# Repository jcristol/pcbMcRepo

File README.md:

# pcbMcRepo
A hearty and fully functional meal from the fryer of Texas Guadaloop Industries Ltd. Limited time supply

- See the circuit schematic look at .sch files
- See the PCB layout look at .pcb files
- Open these files I suggest you use KiCAD
- The circuit below is the myrio circuit

### Picture of the PCB

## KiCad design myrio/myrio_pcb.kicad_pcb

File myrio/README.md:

# pcbMcRepo
A hearty and fully functional meal from the fryer of Texas Guadaloop Industries Ltd. Limited time supply

### [Google Doc](https://docs.google.com/document/d/14EoQXWibSE1bEbYZ6znybRfnlsqGPjPEWS3_kOOsmus/edit)

## Work Division
__3 branch__ 

__Cody__

__Josh__

__Master merge on agreement__

### Design Comments feel free to edit

## BLOCKERS
1. Screw Terminals footprints need to be exact so the labels will fit
2. Ethernet Pin outs
3. Do we need pull up resistors on the bus?
4. The i2c stress test. Are the buses too full?
5. Specs on the housing for the myrio pinout on the PCB
6. Measure the diameter of the vin+ and vin- pins
7. Pin out on the power converters?

## EXTRA Features
1. Cody had special connectors for the robot car that we can use for the power and end connection
2. The screw terminals for extra shit

## Ben Questions
__Ethernet Pin Outs__

__i2c stress test how did that go?__ 

__Are the i2c buses full and will this change the PCB design?__

__Do we need Pull up resistors on the bus?__

__Measure the diameter of power board vin+ and vin- pins__

__Pin out on the par converters i.e. vin, gnd, vout+, vout-__

__Details on what extra screw terminals we need and how you want them arranged?__

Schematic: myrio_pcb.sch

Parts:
220ohm1, 220ohm2, 220ohm3, 220ohm4: R; R_Axial_DIN0204_L3.6mm_D1.6mm_P5.08mm_Horizontal
C1, C2, C3, C4, C5, C6, C7, C9: C; CP_Radial_D5.0mm_P2.50mm
D1, D2, D3, D4, D5, D6, D7, D8, D9, D10, D11, D12, D13, D14, D15, D16, D17, D18, D19, D20, D22: D; D_DO-35_SOD27_P5.08mm_Vertical_AnodeUp
D23: LED; LED_D5.0mm
H1: BMP180; bmp180
J1, J2, J3, J4: CONN_02X03; Pin_Header_Straight_2x03_Pitch2.54mm
P1, P2: CONN_02X17; Socket_Strip_Straight_2x17_Pitch2.54mm
Q1, Q2, Q3, Q4, Q5, Q6, Q7, Q8, Q9, Q10, Q11, Q12, Q13, Q14, Q15, Q16, Q17, Q18, Q19, Q20: PN2222A; TO-92_Inline_Narrow_Oval
R1, R2, R3, R4, R5, R6, R7, R8, R9, R10, R11, R12, R13, R14, R15, R16, R17, R18, R19, R20, R22, R23, R24, R25, R26, R27, R28, R29: R; R_Axial_DIN0204_L3.6mm_D1.6mm_P5.08mm_Horizontal
R21: 500; R_Axial_DIN0204_L3.6mm_D1.6mm_P5.08mm_Horizontal
R30, R31: 12K; R_Axial_DIN0204_L3.6mm_D1.6mm_P5.08mm_Horizontal
R32, R33: 2K; R_Axial_DIN0204_L3.6mm_D1.6mm_P5.08mm_Horizontal
RE1, RE2, RE3, RE4, RE5, RE6, RE7, RE8, RE9, RE10, RE11, RE12, RE13, RE14, RE15, RE16, RE17, RE18, RE19, RE20: relay
S2, S4, S5, S6: 2pinscrew; screwinconnector++
T1, T2, T3, T4: Phoenix_Contact_1935187
U1, U2, U8: stacked-DB9; DB9-doublestacked_PR
U3, U4, U5, U7, U14, U15: stacked-rj45-LED; stacked-rj45_Final++
U6: BNO055
U10, U11, U13: INA219

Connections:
2way_close_1: RE6.1 (NC), U14.2
2way_close_2: RE7.1 (NC), U14.5
2way_close_3: RE8.1 (NC), U14.10
2way_ctrl_1: P1.11, R1.2
2way_ctrl_1_coil-: D1.2 (A), Q1.3 (C), RE6.9 (coil-)
2way_ctrl_2: P1.13, R2.2
2way_ctrl_2_coil-: D2.2 (A), Q2.3 (C), RE7.9 (coil-)
2way_ctrl_3: P1.15, R3.2
2way_ctrl_3_coil-: D3.2 (A), Q3.3 (C), RE8.9 (coil-)
2way_open_1: RE6.10 (NO), U14.1
2way_open_2: RE7.10 (NO), U14.4
2way_open_3: RE8.10 (NO), U14.9
3way_close_1: RE14.1 (NC), U14.13
3way_close_2: RE16.1 (NC), U15.2
3way_ctrl_1a: P1.17, R9.2
3way_ctrl_1a_coil-: D9.2 (A), Q9.3 (C), RE14.9 (coil-)
3way_ctrl_1b: P1.19, R15.2
3way_ctrl_1b_coil-: D15.2 (A), Q15.3 (C), RE13.9 (coil-)
3way_ctrl_2a: P1.21, R10.2
3way_ctrl_2a_coil-: D10.2 (A), Q10.3 (C), RE16.9 (coil-)
3way_ctrl_2b: P1.23, R16.2
3way_ctrl_2b_coil-: D16.2 (A), Q16.3 (C), RE15.9 (coil-)
3way_port2_1: RE13.1 (NC), U14.12
3way_port2_2: RE15.1 (NC), U15.1
3way_port3_1: RE13.10 (NO), U14.15
3way_port3_2: RE15.10 (NO), U15.3
5V: D1.1 (K), D2.1 (K), D3.1 (K), D4.1 (K), D5.1 (K), D6.1 (K), D7.1 (K), D8.1 (K), D9.1 (K), D10.1 (K), D11.1 (K), D12.1 (K), D13.1 (K), D14.1 (K), D15.1 (K), D16.1 (K), D17.1 (K), D18.1 (K), D19.1 (K), D20.1 (K), R22.1, R23.1, R24.1, R25.1, R26.1, R27.1, R28.1, R29.1, RE1.2 (coil+), RE1.10 (NO), RE2.2 (coil+), RE2.10 (NO), RE3.2 (coil+), RE3.10 (NO), RE4.2 (coil+), RE4.10 (NO), RE5.2 (coil+), RE6.2 (coil+), RE7.2 (coil+), RE8.2 (coil+), RE9.2 (coil+), RE9.10 (NO), RE10.2 (coil+), RE10.10 (NO), RE11.2 (coil+), RE11.10 (NO), RE12.2 (coil+), RE12.10 (NO), RE13.2 (coil+), RE14.2 (coil+), RE15.2 (coil+), RE16.2 (coil+), RE17.2 (coil+), RE17.10 (NO), RE18.2 (coil+), RE19.2 (coil+), RE20.2 (coil+), T3.4
12V: C1.1, C2.1, T1.1, T3.1, T4.3, U10.8 (VIN+), U11.7 (VIN-)
24V: C4.1, C9.1, RE5.10 (NO), T1.4, U7.1, U7.4, U8.9, U8.11, U13.8 (VIN+), U15.7, U15.8, U15.11, U15.14
24V_activation: RE5.5 (load1), RE5.6 (load2), RE6.5 (load1), RE6.6 (load2), RE7.5 (load1), RE7.6 (load2), RE8.5 (load1), RE8.6 (load2), RE14.5 (load1), RE14.6 (load2), RE16.5 (load1), RE16.6 (load2)
A0: P2.3, S2.1
A1: P2.5, S2.2
DGND: 220ohm1.2, 220ohm2.2, 220ohm3.2, 220ohm4.2, C1.2, C2.2, C3.2, C4.2, C5.2, C6.2, C7.2, C9.2, H1.2 (gnd), P1.6, P1.8, P1.12, P1.16, P1.20, P1.24, P1.28, P1.30, P2.6, P2.8, P2.12, P2.16, P2.20, P2.24, P2.28, P2.30, Q1.1 (E), Q2.1 (E), Q3.1 (E), Q4.1 (E), Q5.1 (E), Q6.1 (E), Q7.1 (E), Q8.1 (E), Q9.1 (E), Q10.1 (E), Q11.1 (E), Q12.1 (E), Q13.1 (E), Q14.1 (E), Q15.1 (E), Q16.1 (E), Q17.1 (E), Q18.1 (E), Q19.1 (E), Q20.1 (E), R21.2, R32.2, R33.2, RE1.1 (NC), RE2.1 (NC), RE3.1 (NC), RE4.1 (NC), RE9.1 (NC), RE10.1 (NC), RE11.1 (NC), RE12.1 (NC), RE17.1 (NC), RE19.1 (NC), RE20.1 (NC), S6.2, T1.2, T1.3, T2.2, T2.4, T3.2, T3.3, T4.4, U1.5, U1.6, U1.7, U1.8, U1.9, U1.14, U1.15, U1.16, U1.17, U1.18, U2.5, U2.6, U2.7, U2.8, U2.9, U2.14, U2.15, U2.16, U2.17, U2.18, U3.2, U3.5, U3.10, U3.13, U4.2, U4.5, U4.10, U4.13, U5.2, U5.5, U5.10, U5.13, U6.3 (gnd), U7.2, U7.5, U7.10, U7.13, U8.5, U8.12, U10.2 (Gnd), U11.2 (Gnd), U13.2 (Gnd), U14.3, U14.7, U14.11, U14.16, U15.6
unnamed: D23.1 (K), R21.1
unnamed: Q1.2 (B), R1.1
unnamed: Q2.2 (B), R2.1
unnamed: Q3.2 (B), R3.1
unnamed: Q4.2 (B), R4.1
unnamed: Q5.2 (B), R5.1
unnamed: Q6.2 (B), R6.1
unnamed: Q7.2 (B), R7.1
unnamed: Q8.2 (B), R8.1
unnamed: Q9.2 (B), R9.1
unnamed: Q10.2 (B), R10.1
unnamed: Q11.2 (B), R11.1
unnamed: Q12.2 (B), R12.1
unnamed: Q13.2 (B), R13.1
unnamed: Q14.2 (B), R14.1
unnamed: Q15.2 (B), R15.1
unnamed: Q16.2 (B), R16.1
unnamed: Q17.2 (B), R17.1
unnamed: Q18.2 (B), R18.1
unnamed: Q19.2 (B), R19.1
unnamed: Q20.2 (B), R20.1
unnamed: RE13.5 (load1), RE14.10 (NO)
unnamed: RE15.5 (load1), RE16.10 (NO)
Tof_Ctrl_1: P2.11, R5.2
Tof_Ctrl_1_coil-: D5.2 (A), Q5.3 (C), RE1.9 (coil-)
Tof_Ctrl_2: P2.13, R11.2
Tof_Ctrl_2_coil-: D11.2 (A), Q11.3 (C), RE9.9 (coil-)
Tof_Ctrl_3: P2.15, R6.2
Tof_Ctrl_3_coil-: D6.2 (A), Q6.3 (C), RE2.9 (coil-)
Tof_Ctrl_4: P2.17, R12.2
Tof_Ctrl_4_coil-: D12.2 (A), Q12.3 (C), RE10.9 (coil-)
Tof_Ctrl_5: P2.19, R7.2
Tof_Ctrl_5_coil-: D7.2 (A), Q7.3 (C), RE3.9 (coil-)
Tof_Ctrl_6: P2.21, R13.2
Tof_Ctrl_6_coil-: D13.2 (A), Q13.3 (C), RE11.9 (coil-)
Tof_Ctrl_7: P2.23, R8.2
Tof_Ctrl_7_coil-: D8.2 (A), Q8.3 (C), RE4.9 (coil-)
Tof_Ctrl_8: P2.25, R14.2
Tof_Ctrl_8_coil-: D14.2 (A), Q14.3 (C), RE12.9 (coil-)
battery: C3.1, T2.3, T4.1
battery+fuse: C7.1, D23.2 (A), T4.2, U11.8 (VIN+)
brake_pwr: RE19.10 (NO), RE20.10 (NO), U13.7 (VIN-)
critical_scl: J1.6, J3.6, P2.32, R23.2, U3.3, U3.7, U3.11, U3.15
critical_sda: J2.6, J4.6, P2.34, R22.2, U3.6, U3.8, U3.14, U3.16
friction_coil-: D19.2 (A), Q19.3 (C), RE19.9 (coil-)
friction_ctrl: P1.27, R19.2
friction_pwr: RE18.5 (load1), RE18.6 (load2), RE19.5 (load1), RE19.6 (load2), U1.1, U1.2, U1.3, U1.4, U2.1, U2.2, U2.3, U2.4
i2c_scl_2: J1.2, J3.2, P2.22, R27.2, S4.1
i2c_scl_3: P1.22, R29.2, S5.1
i2c_sda_2: J2.2, J4.2, P2.26, R26.2, S4.2
i2c_sda_3: P1.26, R28.2, S5.2
laser1: P2.29, U7.11
laser2: P2.31, U7.15
laser_digital1: P2.18, R30.2, R33.1
laser_digital2: P1.25, R31.2, R32.1
magnetic_coil-: D20.2 (A), Q20.3 (C), RE20.9 (coil-)
magnetic_ctrl: P1.29, R20.2
magnetic_pwr: D22.2 (A), RE20.5 (load1), RE20.6 (load2), U1.10, U1.11, U1.12, U1.13, U2.10, U2.11, U2.12, U2.13
main_laser1: R30.1, U7.3
main_laser2: R31.1, U7.7
myRIO_12V: C5.1, T2.1, U10.7 (VIN-)
non_critical_scl: H1.3 (scl), J1.1, J3.1, P1.32, R25.2, U6.5 (scl), U10.3 (Scl), U11.3 (Scl), U13.3 (Scl)
non_critical_sda: H1.4 (sda), J2.1, J4.1, P1.34, R24.2, U6.4 (sda), U10.4 (Sda), U11.4 (Sda), U13.4 (Sda)
pressure1-: 220ohm1.1, P1.3, U15.4
pressure2-: 220ohm2.1, P1.5, U15.5
pressure3-: 220ohm3.1, P1.7, U15.9
pressure4-: 220ohm4.1, P1.9, U15.10
pressure_activation: P1.31, R4.2
pressure_activation_coil-: D4.2 (A), Q4.3 (C), RE5.9 (coil-)
sense_pwr: C6.1, H1.1 (5V), RE17.5 (load1), RE17.6 (load2), U5.1, U5.4, U5.9, U5.12, U6.1 (Vin), U7.9, U7.12, U10.1 (Vin), U11.1 (Vin), U13.1 (Vin)
sense_pwr_coil-: D18.2 (A), Q18.3 (C), RE17.9 (coil-)
sense_pwr_ctrl: P2.27, R18.2
stress_scl: J3.3, J3.4, U5.3, U5.7, U5.11, U5.15
stress_sda: J4.3, J4.4, U5.6, U5.8, U5.14, U5.16
to_cap: D22.1 (K), RE18.1 (NC), S6.1
to_cap_coil-: D17.2 (A), Q17.3 (C), RE18.9 (coil-)
to_cap_ctrl: P1.18, R17.2
tof1_power: RE1.6 (load2), U3.1
tof2_power: RE9.6 (load2), U3.4
tof3_power: RE2.6 (load2), U3.9
tof4_power: RE10.6 (load2), U3.12
tof5_power: RE3.6 (load2), U4.1
tof6_power: RE11.6 (load2), U4.4
tof7_power: RE4.6 (load2), U4.9
tof8_power: RE12.6 (load2), U4.12
tof_scl: J1.3, J1.4, U4.3, U4.7, U4.11, U4.15
tof_sda: J2.3, J2.4, U4.6, U4.8, U4.14, U4.16

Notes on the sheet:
AGND
AO0
AO1
DGND
UART.RX
DIO11 / ENC.A
UART.TX
DIO12 / ENC.B
DIO13
DIO14 / I2C.SCL
+5V
AI0
AI1
AI2
AI3
DIO0
DIO1
DIO2
DIO3
DIO4
DIO5 / SPI.CLK
DIO6 / SPI.MISO
DIO7 / SPI.MOSI
DIO8 / PWM0
DIO9 / PWM1
DIO10 / PWM2
+3.3V
DIO15 / I2C.SDA
need to figure out the acc read and other signals connected to the far side of the myrio board
TOF Relays
TOF BJTs
Time Of Flight
N-Way Control
2-Way Relays
2-Way BJT
3-Way Relays
3-Way BJT
Pressure Activation
BJT-Relay Circuits
Lock BJT

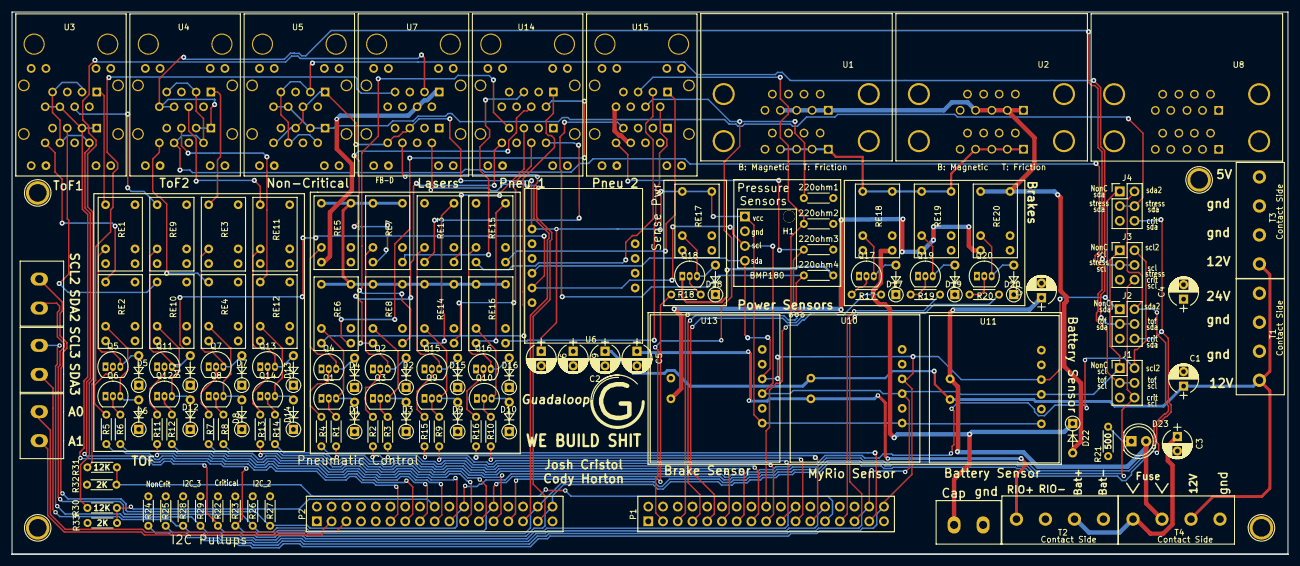
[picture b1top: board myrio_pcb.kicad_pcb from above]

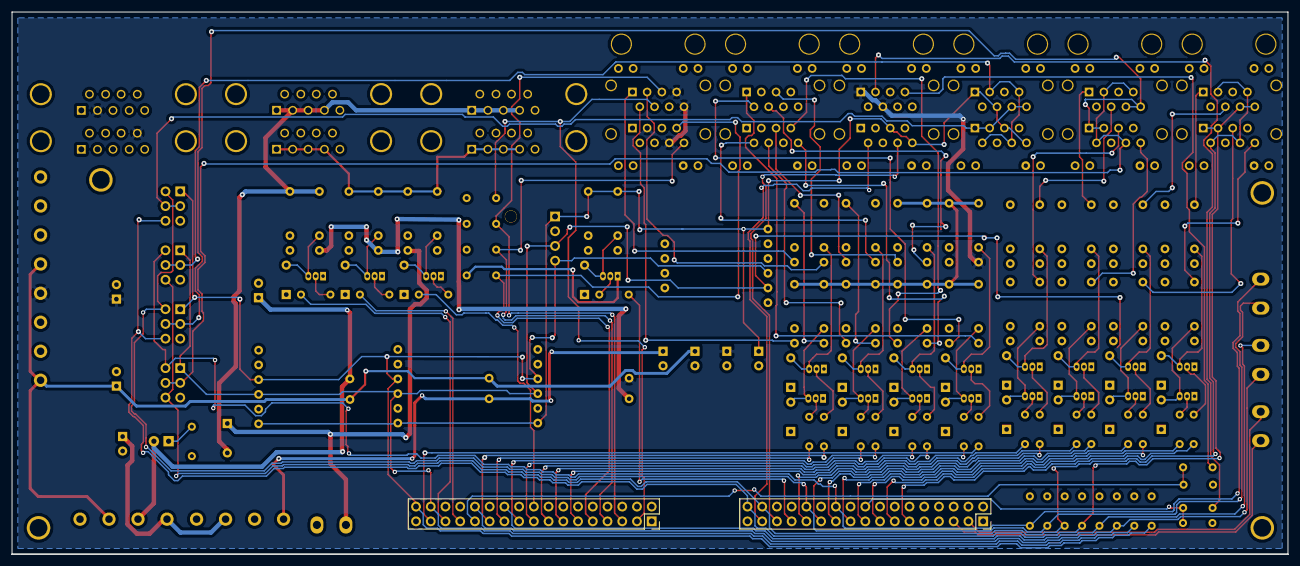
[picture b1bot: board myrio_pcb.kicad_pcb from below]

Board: 4 copper layers, 220.0 x 93.5 mm, 135 parts (2 on the bottom side), 120 nets.

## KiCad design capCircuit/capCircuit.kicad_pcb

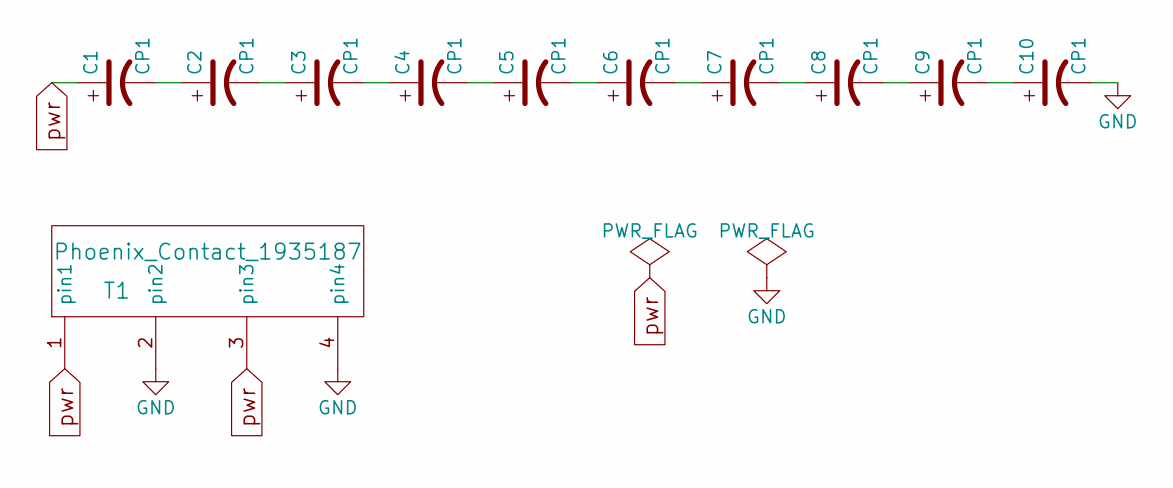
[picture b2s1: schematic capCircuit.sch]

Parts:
C1, C2, C3, C4, C5, C6, C7, C8, C9, C10: CP1; CP_Radial_D10.0mm_P3.50mm
T1: Phoenix_Contact_1935187

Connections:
GND: C10.2, T1.2, T1.4
unnamed: C1.2, C2.1
unnamed: C2.2, C3.1
unnamed: C3.2, C4.1
unnamed: C4.2, C5.1
unnamed: C5.2, C6.1
unnamed: C6.2, C7.1
unnamed: C7.2, C8.1
unnamed: C8.2, C9.1
unnamed: C9.2, C10.1
pwr: C1.1, T1.1, T1.3

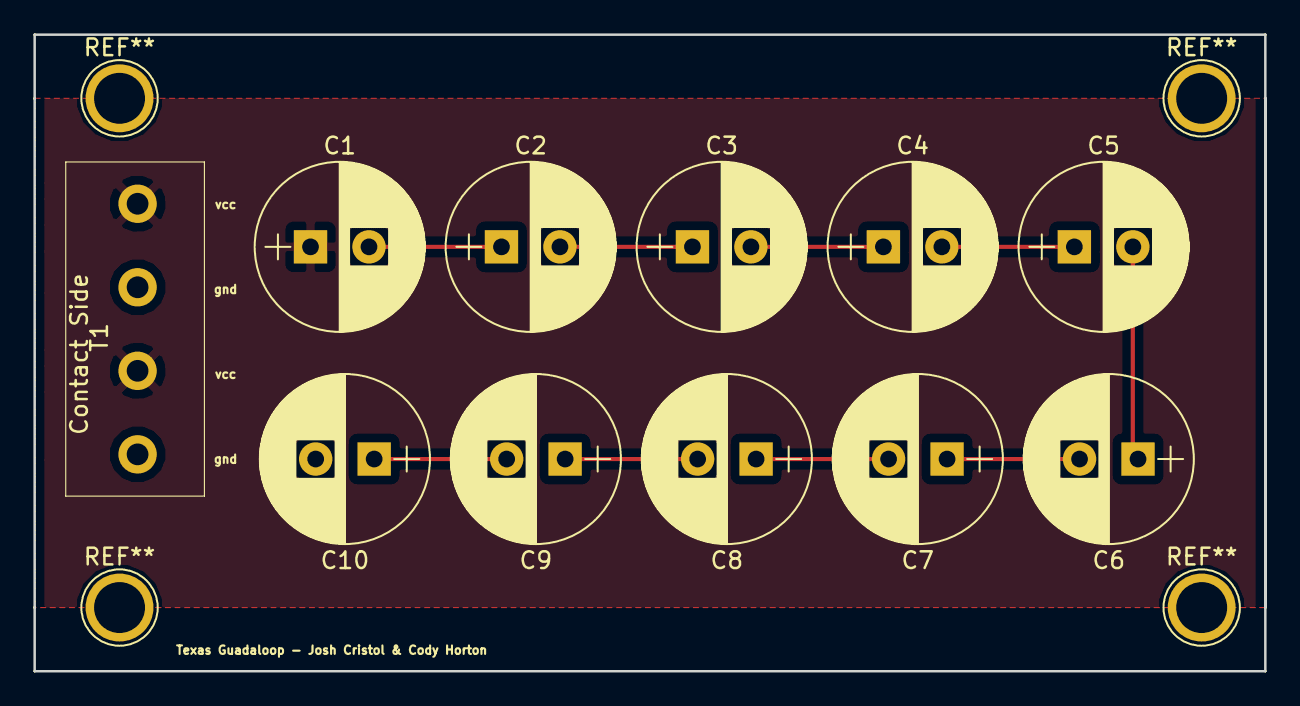
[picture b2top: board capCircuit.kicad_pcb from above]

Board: 2 copper layers, 73.7 x 38.1 mm, 11 parts (0 on the bottom side), 11 nets.

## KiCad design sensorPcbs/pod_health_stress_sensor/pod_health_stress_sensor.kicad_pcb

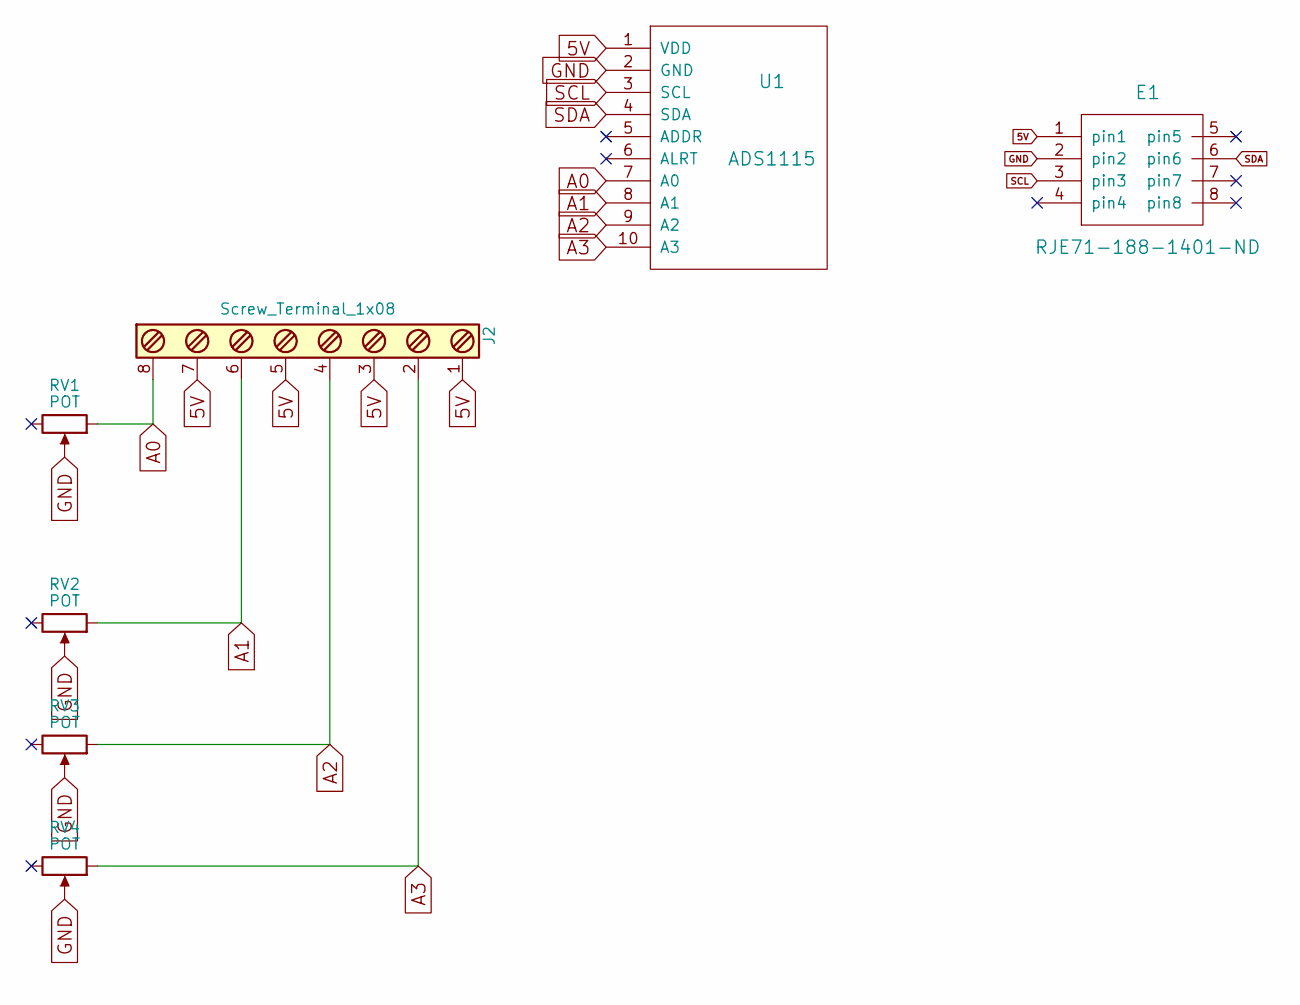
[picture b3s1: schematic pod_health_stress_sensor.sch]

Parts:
E1: RJE71-188-1401-ND
J2: Screw_Terminal_1x08; TerminalBlock_Pheonix_MKDS1.5-8pol
RV1, RV2, RV3, RV4: POT; Potentiometer_Trimmer_Bourns_3296W
U1: ADS1115

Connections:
5V: E1.1, J2.1, J2.3, J2.5, J2.7, U1.1 (VDD)
A0: J2.8, RV1.1, U1.7 (A0)
A1: J2.6, RV2.1, U1.8 (A1)
A2: J2.4, RV3.1, U1.9 (A2)
A3: J2.2, RV4.1, U1.10 (A3)
GND: E1.2, RV1.2, RV2.2, RV3.2, RV4.2, U1.2 (GND)
SCL: E1.3, U1.3 (SCL)
SDA: E1.6, U1.4 (SDA)

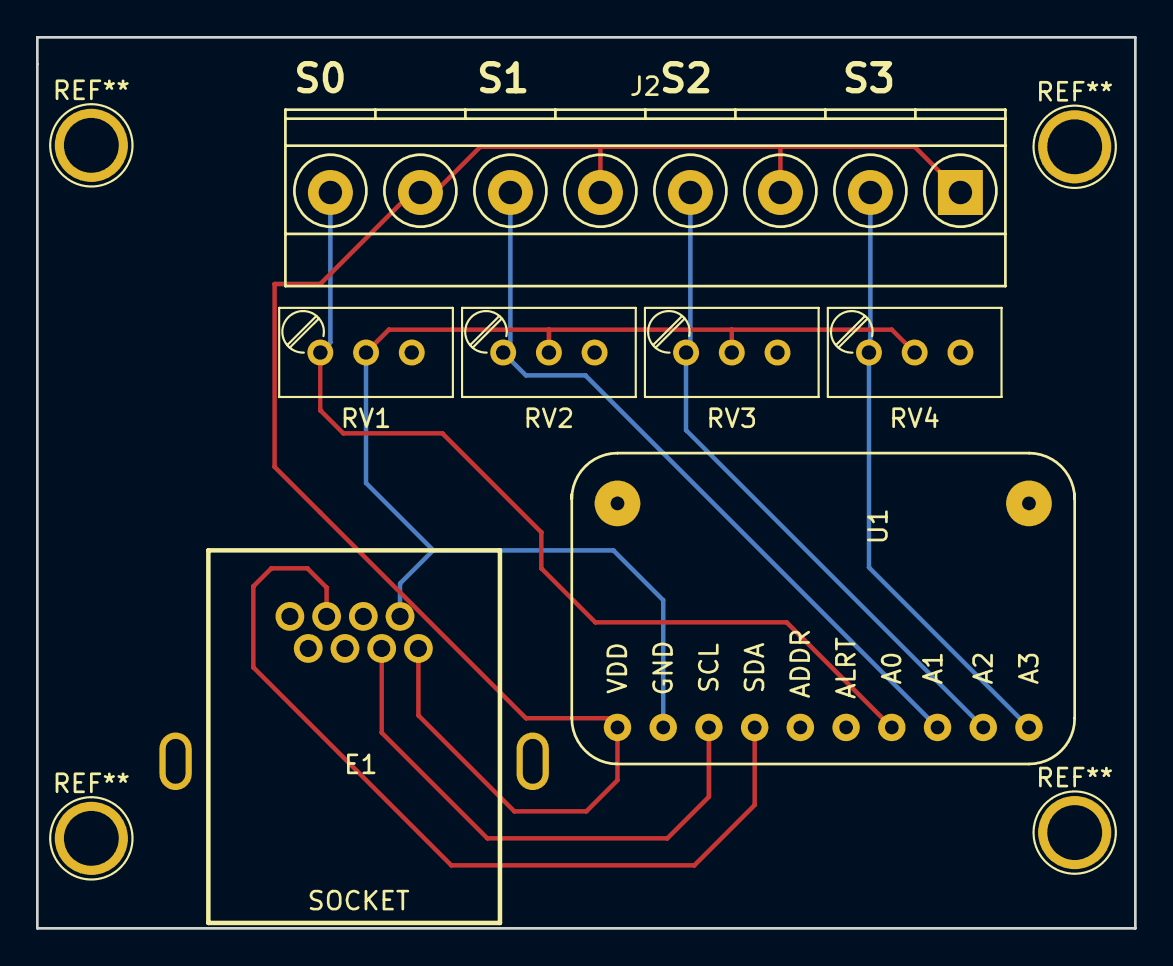
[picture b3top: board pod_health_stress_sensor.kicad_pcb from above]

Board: 2 copper layers, 61.0 x 49.5 mm, 7 parts (0 on the bottom side), 8 nets.

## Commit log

2017-06-04 First commit i love mcribs and other things that taste good This revision will serve to fix many of the issues in the google doc link in the README by the illustrious Ben James
2017-06-04 added some critical stuffs to the README
2017-06-04 quick fix
2017-06-04 added some stuff for Ben to answer
2017-06-04 changes README
2017-06-05 the schematic looks good just have to add the screw terminals and ethernet footprints. I also edited the pcb file so that it has some helpful test on the left and right side
2017-06-05 cleaned schematic a bit and messed around the 12V battery signal have run a drc and annotate everything checks out
2017-06-05 added screwconnector++ use this instead of the regular screw terminals
2017-06-05 added stacked-rj45_Final++ this is the new ethernet connector
2017-06-06 donezo
2017-06-12 new revision on this branch
2017-06-12 the new commit changedthe nap pins
2017-06-14 hyerploop pcb mcrepo
2017-07-16 updating the file strucutre
2017-07-16 added myrio
2017-07-17 moved the readme over here
2017-07-17 added it too
2017-07-17 flipped the 2ways functionality
2017-07-17 added the router screw terminal
2017-07-17 readme comments
2017-07-19 undid changes writing stuff in the README
2017-07-19 flipped nc and no on the 2way relays
2017-07-19 changed sensor powers to be noramlly connected to ground
2017-07-19 made the battery fuse
2017-07-19 made the router screw terminal
2017-07-20 added the LED haven't connected it to the switch yet
2017-07-20 made switch schematic
2017-07-20 adding switch schematic
2017-07-20 added in the switch footprint and switch circuit into the sketch
2017-07-20 updated the schematic
2017-07-20 made schematic and footprint for 4 pin screw terminal
2017-07-20 made the screw terminal changes
2017-07-20 renamed some stuff had to add some pwer flags so kicad would stop bitching. Dont worry though they do absolutly nothing to the circuit
2017-07-20 fixed the resistor value
2017-07-20 added a sensor PCBS folder
2017-07-20 made a new ethernet footprint and changed the foot print schematic structure in the sensorBoard shit
2017-07-20 changed all the sensor PCB schematics and added the global component schematic library into each project
2017-07-20 added all the ferkin new ethernet shields to the sensor pcbs
2017-07-20 updated the README for Cody
2017-07-21 made the cap circuit
2017-07-21 added gitignore
2017-07-21 fixed the laser circuit
2017-07-21 not sure what hanged
2017-07-21 fixed the tof according to viks wants
2017-07-25 layout done, still tracing
2017-07-27 considering capacitors
2017-07-30 traces for days
2017-07-31 more traces done
2017-07-31 made small changes according to feedback
2017-07-31 made changes according to 7-31 feedback doc
2017-07-31 commiting the schematic changes
2017-08-01 donezo mcfunzo
2017-08-02 done for real this time
2017-08-02 made the anal rings bigger
2017-08-08 fixed mountinghole short
2018-01-09 updated the README
2018-01-09 adding the picture
